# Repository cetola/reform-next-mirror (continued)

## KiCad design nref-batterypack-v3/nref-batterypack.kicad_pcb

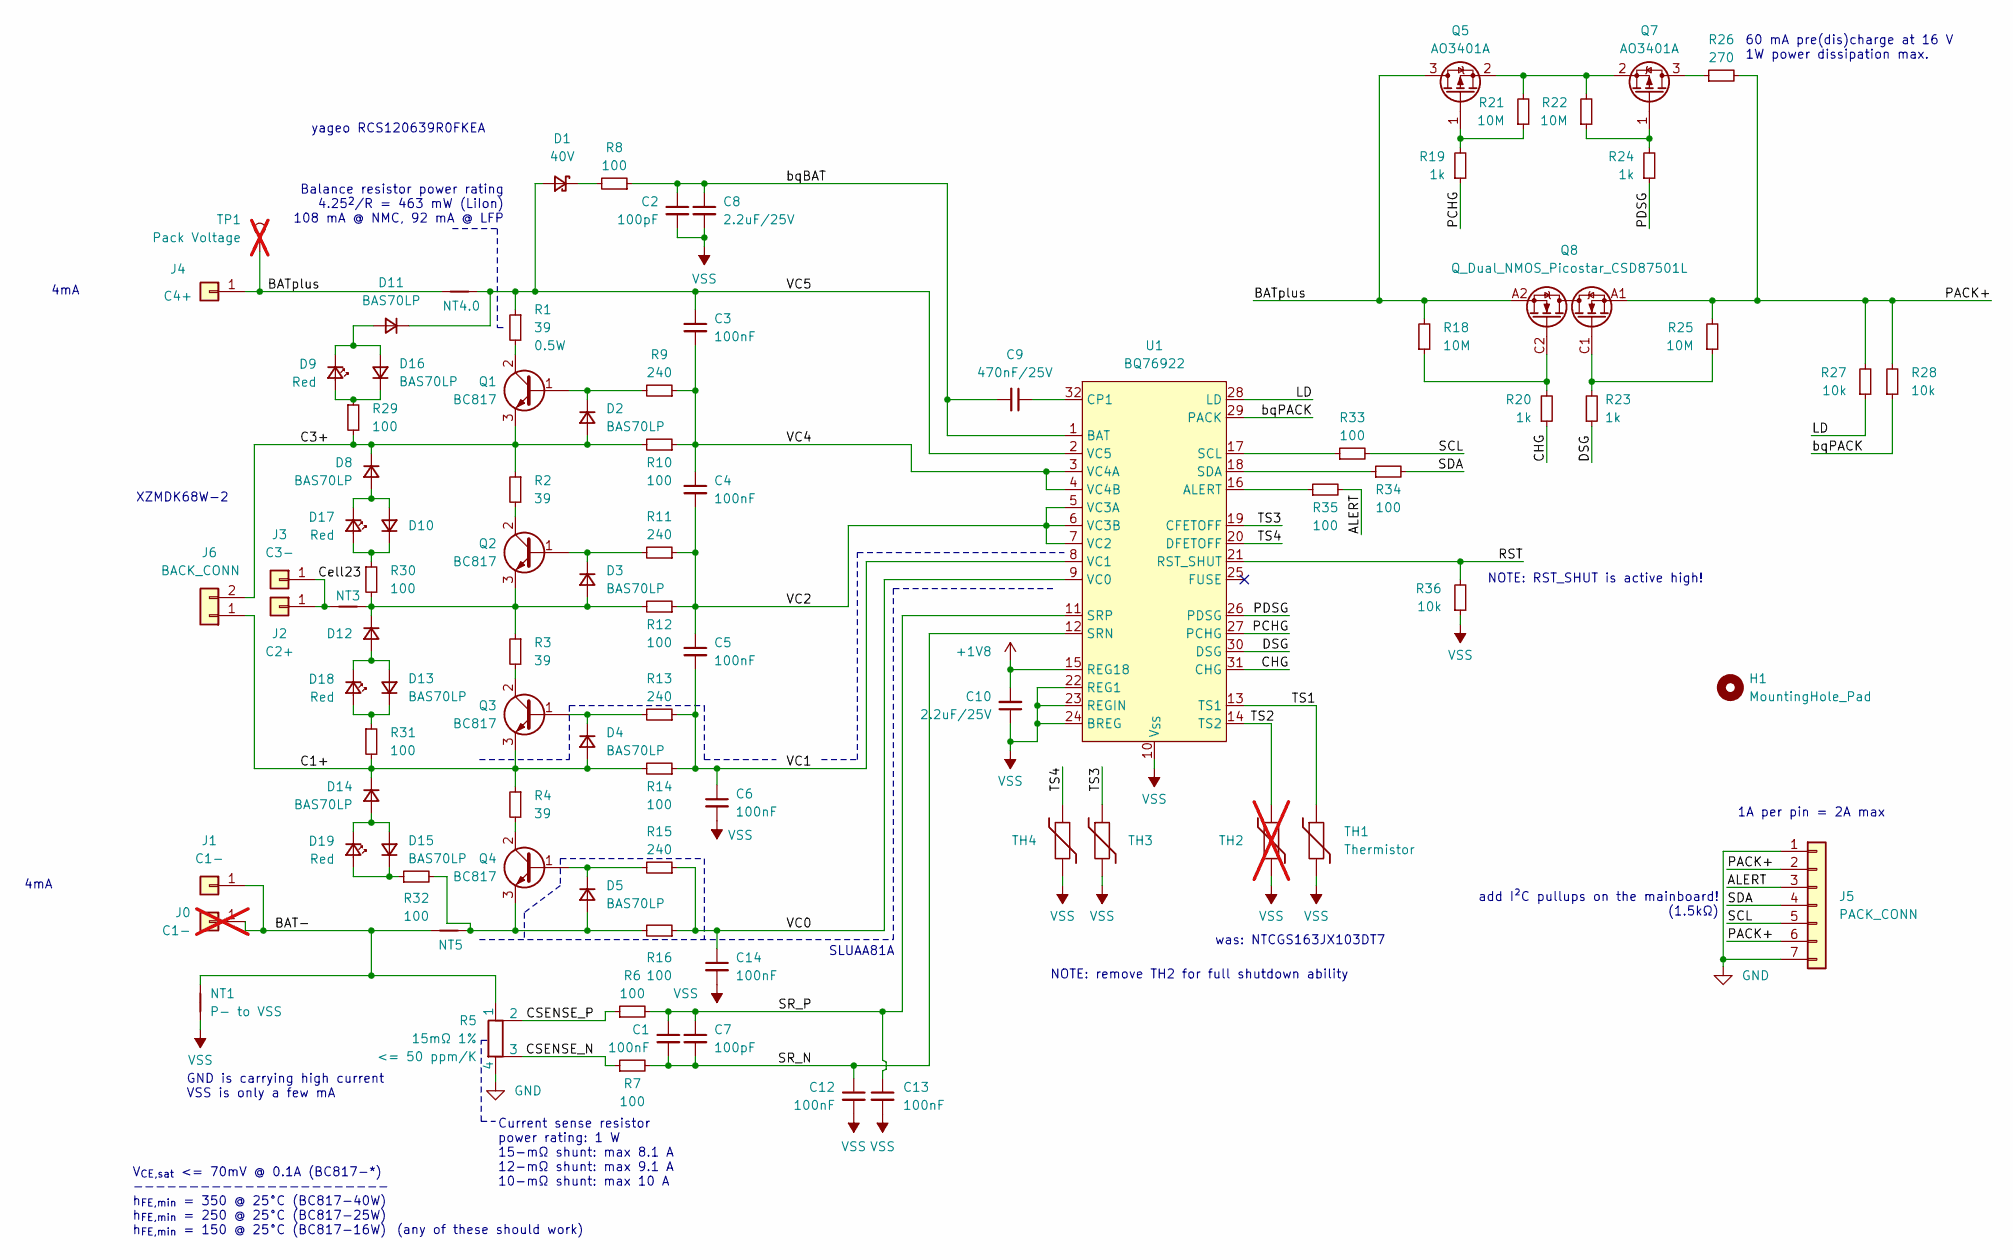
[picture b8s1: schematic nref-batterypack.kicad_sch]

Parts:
C1, C3, C4, C5, C6, C12, C13, C14: 100nF; C_0402_1005Metric; MPN CL05B104KO5NNNC; LCSC C1525
C2, C7: 100pF; C_0402_1005Metric; MPN 0402CG101J500NT; LCSC C1546
C8, C10: 2.2uF/25V; C_0402_1005Metric; MPN GRM155R61E225ME15D; LCSC C72203
C9: 470nF/25V; C_0402_1005Metric; MPN CL05A474KA5NNNC; LCSC C92361
D1: 40V; D_SOD-323; MPN B140WS-7; LCSC C95171
D2, D3, D4, D5, D8, D10, D11, D12, D13, D14, D15, D16: BAS70LP; D_SOD-882; MPN BAS70LP-7B; LCSC C134385
D9, D17, D18, D19: Red; LED_0402_1005Metric; MPN NCD0402R1; LCSC C130719
H1: MountingHole_Pad; MountingHole_2.2mm_M2
J0: C1-; TestPoint_Pad_D1.0mm; MPN DNP; not fitted
J1: C1-; MYOUNG_MY-FJ-115; MPN MY-FJ-115; LCSC C5457098
J2: C2+; Mill-Max_2036-X-57; MPN 2036-3-57-15-00-00-03-0; LCSC C20777560
J3: C3-; MYOUNG_MY-FJ-115; MPN MY-FJ-115; LCSC C5457098
J4: C4+; Mill-Max_2036-X-57; MPN 2036-3-57-15-00-00-03-0; LCSC C20777560
J5: PACK_CONN; JST_SH_BM07B-SRSS-TB_1x07-1MP_P1.00mm_Vertical; MPN BM07B-SRSS-TB; LCSC C160393
J6: BACK_CONN; JST_SH_SM02B-SRSS-TB_1x02-1MP_P1.00mm_Horizontal; MPN SM02B-SRSS-TB; LCSC C160402
NT1: P- to VSS; NetTie-2_SMD_Pad0.5mm; MPN DNP
NT3, NT5: NetTie-2_SMD_Pad0.5mm; MPN DNP
NT4.0: P- to GND; NetTie-2_SMD_Pad0.5mm; MPN DNP
Q1, Q2, Q3, Q4: BC817; SOT-23; MPN BC817-25LT1G; LCSC C12766
Q5, Q7: AO3401A; SOT-23; MPN AO3401A; LCSC C15127
Q8: Q_Dual_NMOS_Picostar_CSD87501L; TI_PICOSTAR_LGA-10_3.37x1.47mm_P0.65mm; MPN CSD87501L; LCSC C2841784
R1, R2, R3, R4: 39; R_1210_3225Metric; MPN FRP1206J390 TS; LCSC C5713422
R5: 15mΩ 1%; R_Shunt_Kelvin_Littlefuse_L4CA; MPN PE0612FKF070R015L; LCSC C6142742
R6, R7, R8, R10, R12, R14, R16, R29, R30, R31, R32, R33, R34, R35: 100; R_0402_1005Metric; MPN 0402WGF1000TCE; LCSC C25076
R9, R11, R13, R15: 240; R_0402_1005Metric; MPN RC0402FR-07240RL; LCSC C114755
R18, R21, R22, R25: 10M; R_0402_1005Metric; MPN RC0402FR-0710ML; LCSC C138067
R19, R20, R23, R24: 1k; R_0402_1005Metric; MPN 0402WGF1001TCE; LCSC C11702
R26: 270; R_1812_4532Metric; MPN GR1812J270RT4G00; LCSC C49656236
R27, R28, R36: 10k; R_0402_1005Metric; MPN 0402WGF1002TCE; LCSC C25744
TH1, TH3, TH4: Thermistor; R_0402_1005Metric; MPN CMFX 103F3435; LCSC C2889040
TH2: Thermistor; R_0402_1005Metric; MPN NTCGS103JX103DT7; LCSC C24890359; not fitted
TP1: Pack Voltage; TestPoint_Pad_1.0x1.0mm; MPN DNP; not fitted
U1: BQ76922; Texas_RSN_WQFN-32-1EP_4x4mm_P0.4mm_EP2.8x2.8mm; MPN BQ76922; LCSC C33651534

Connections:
+1V8: C10.2, U1.15 (REG18)
/ALERT: J5.3, R35.2
/BAT-: J0.1 (Pin_1_1), J1.1 (Pin_1_1), NT1.2, NT5.2, R5.1
/BATplus: J4.1 (Pin_1_1), NT4.0.2, Q5.3 (D), Q8.A2 (S2), Q8.B2 (S2), Q8.D2 (S2), Q8.E2 (S2), R18.2, TP1.1 (1_1)
/C1+: D4.2 (A), D14.1 (K), J6.1, Q3.3 (E), R4.1, R14.2, R31.2
/C3+: D2.2 (A), D8.1 (K), J6.2, Q1.3 (E), R2.1, R10.2, R29.2
/CHG: R20.1, U1.31 (CHG)
/CSENSE_N: R5.3, R7.1
/CSENSE_P: R5.2, R6.1
/Cell23: J2.1 (Pin_1_1), J3.1 (Pin_1_1), NT3.2
/DSG: R23.1, U1.30 (DSG)
/LD: R27.1, U1.28 (LD)
/PACK+: J5.2, J5.6, Q8.A1 (S1), Q8.B1 (S1), Q8.D1 (S1), Q8.E1 (S1), R25.2, R26.2, R27.2, R28.2
/PCHG: R19.1, U1.27 (PCHG)
/PDSG: R24.1, U1.26 (PDSG)
/RST: R36.2, U1.21 (RST_SHUT)
/SCL: J5.5, R33.2
/SDA: J5.4, R34.2
/SR_N: C1.2, C7.2, C12.1, R7.2, U1.12 (SRN)
/SR_P: C1.1, C7.1, C13.1, R6.2, U1.11 (SRP)
/TS1: TH1.1, U1.13 (TS1)
/TS2: TH2.1, U1.14 (TS2)
/TS3: TH3.1, U1.19 (CFETOFF)
/TS4: TH4.1, U1.20 (DFETOFF)
/VC0: C14.1, R15.1, R16.1, U1.9 (VC0)
/VC1: C5.2, C6.1, R13.1, R14.1, U1.8 (VC1)
/VC2: C4.2, C5.1, R11.1, R12.1, U1.5 (VC3A), U1.6 (VC3B), U1.7 (VC2)
/VC4: C3.2, C4.1, R9.1, R10.1, U1.3 (VC4A), U1.4 (VC4B)
/VC5: C3.1, D1.2 (A), D11.1 (K), NT4.0.1, R1.1, U1.2 (VC5)
/bqBAT: C2.1, C8.1, C9.2, R8.1, U1.1 (BAT)
/bqPACK: R28.1, U1.29 (PACK)
GND: J5.1, J5.7, R5.4
unnamed: D1.1 (K), R8.2
unnamed: D2.1 (K), Q1.1 (B), R9.2
unnamed: D3.1 (K), Q2.1 (B), R11.2
unnamed: D4.1 (K), Q3.1 (B), R13.2
unnamed: D5.2 (A), NT5.1, Q4.3 (E), R16.2, R32.2
unnamed: D5.1 (K), Q4.1 (B), R15.2
unnamed: D8.2 (A), D10.2 (A), D17.1 (K)
unnamed: D10.1 (K), D17.2 (A), R30.1
unnamed: D9.1 (K), D11.2 (A), D16.2 (A)
unnamed: D12.2 (A), D13.2 (A), D18.1 (K)
unnamed: D3.2 (A), D12.1 (K), NT3.1, Q2.3 (E), R3.1, R12.2, R30.2
unnamed: D13.1 (K), D18.2 (A), R31.1
unnamed: D14.2 (A), D15.2 (A), D19.1 (K)
unnamed: D15.1 (K), D19.2 (A), R32.1
unnamed: D9.2 (A), D16.1 (K), R29.1
unnamed: Q1.2 (C), R1.2
unnamed: Q2.2 (C), R2.2
unnamed: Q3.2 (C), R3.2
unnamed: Q4.2 (C), R4.2
unnamed: Q5.1 (G), R19.2, R21.1
unnamed: Q5.2 (S), Q7.2 (S), R21.2, R22.2
unnamed: Q7.3 (D), R26.1
unnamed: Q7.1 (G), R22.1, R24.2
unnamed: Q8.C1 (G1), R23.2, R25.1
unnamed: Q8.C2 (G2), R18.1, R20.2
unnamed: R35.1, U1.16 (ALERT)
unnamed: C9.1, U1.32 (CP1)
unnamed: R33.1, U1.17 (SCL)
unnamed: R34.1, U1.18 (SDA)
VSS: C2.2, C6.2, C8.2, C10.1, C12.2, C13.2, C14.2, NT1.1, R36.1, TH1.2, TH2.2, TH3.2, TH4.2, U1.10 (V_{SS}), U1.22 (REG1), U1.23 (REGIN), U1.24 (BREG), U1.33 (EP)

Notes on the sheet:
4mA
NOTE: RST_SHUT is active high!
GND is carrying high current VSS is only a few mA
XZMDK68W-2
NOTE: remove TH2 for full shutdown ability
was: NTCGS163JX103DT7
V_{CE,sat} <= 70mV @ 0.1A (BC817-*) ----------------------- h_{FE,min} = 350 @ 25°C (BC817-40W) h_{FE,min} = 250 @ 25°C (BC817-25W) h_{FE,min} = 150 @ 25°C (BC817-16W)
(any of these should work)
1A per pin = 2A max
60 mA pre(dis)charge at 16 V 1W power dissipation max.
Current sense resistor power rating: 1 W 15-mΩ shunt: max 8.1 A 12-mΩ shunt: max 9.1 A 10-mΩ shunt: max 10 A
add I²C pullups on the mainboard! (1.5kΩ)
yageo RCS120639R0FKEA
Balance resistor power rating 4.25^{2}/R = 463 mW (LiIon) 108 mA @ NMC, 92 mA @ LFP
SLUAA81A

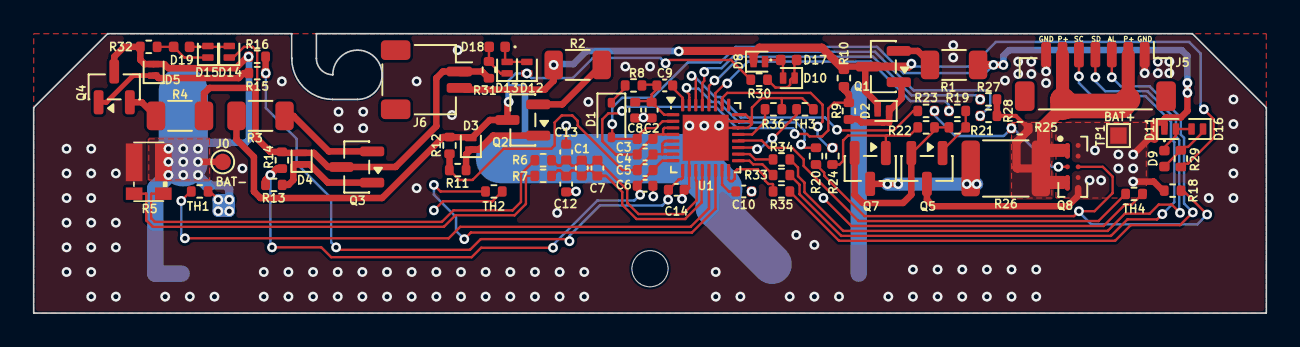
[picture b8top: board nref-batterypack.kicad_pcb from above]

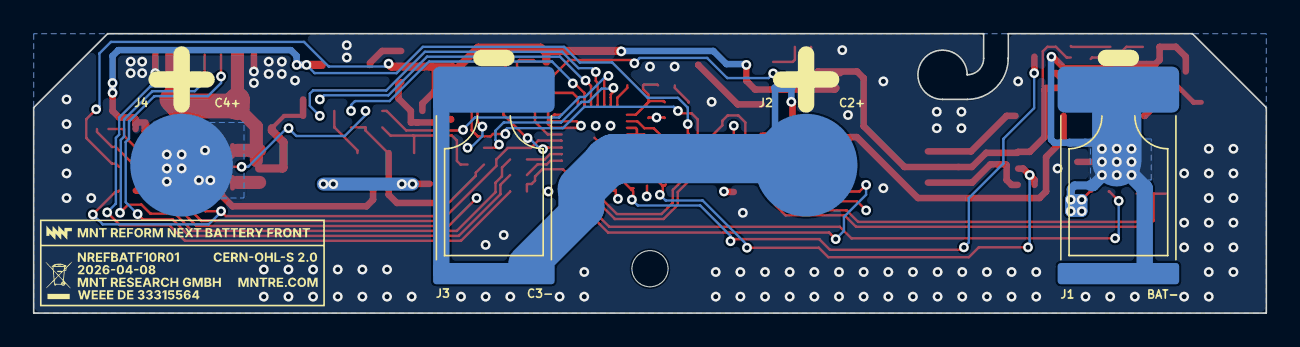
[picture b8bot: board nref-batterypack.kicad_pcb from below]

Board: 4 copper layers, 75.0 x 17.0 mm, 90 parts (7 on the bottom side), 62 nets.

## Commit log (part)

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2024-02-22 add batterypack pcb sketch
2024-02-22 add motherboard pcb early WIP
2024-02-22 add 202401 case proto and fc assembly
2024-03-25 add initial 4S battery pack with hs-switch
2024-04-28 motherboard: upgrade bucks to lm62460; some power layout
2024-04-29 motherboard: lots of connector shuffling and schematics
2024-04-30 motherboard: continue design; almost feature complete
2024-05-24 motherboard: update battery pack connectors, pcie lanes
2024-05-25 motherboard: some initial routing, mostly power
2024-05-27 ports test
2024-05-28 wip of the new version with another bms ic
2024-06-01 motherboard: drv_sup diodes, battery and charger i2c and alerts
2024-06-01 motherboard: consolidate switches and jumpers into one 8x1.27mm dip, liion/lifepo switch
2024-06-04 add a readme
2024-06-05 motherboard: connect extra pcie lanes
2024-06-05 motherboard: schematic done for d-1?
2024-06-05 lots of motherboard routing
2024-06-06 mb: swap some intersecting connectors; more routing
2024-06-07 mb routing snapshot
2024-06-07 mb silkscreen cleaned up
2024-06-07 mb fully routed, logo added
2024-06-11 ports-one WIP
2024-06-11 ports-two initial
2024-06-11 motherboard d-1 production snapshot
2024-06-12 ports one: some routing
2024-06-13 ports 1 routing, ports 2 location tweaks
2024-06-14 ports one: more design and more routing
2024-06-17 motherboard: specify all parts, complete BOM
2024-06-20 ports-one snapshot
2024-06-20 ports two: initial (mostly complete) schematic
2024-06-21 ports two: rough placement of components
2024-06-21 motherboard: add bringup notes to schematic
2024-06-21 batterypack and ports one snapshot
2024-06-21 update README, images
2024-06-21 add mechanical integration 20240604 (ondsel freecad)
2024-06-25 fix some images
2024-06-27 sysctl: first firmware, can negotiate PD
2024-07-04 ports-two: hdmi routing snapshot
2024-07-04 ports two: usb snapshot
2024-07-05 port board two fully routed
2024-07-25 ports two bom adjustments
2024-07-25 WIP batterypack-top polishing
2024-07-26 batterypack: finish front d-1, add back d-1
2024-07-28 v2 of the bms now based on the final outline
2024-07-30 batterypack: pick parts
2024-08-15 fix load switch nmos and gate prot diode polarity
2024-08-15 WIP camera board
2024-08-19 WIP trackpad
2024-08-20 docs: add ports one/two specs and drawings
2024-08-20 add port board three spec
2024-08-20 port boards spec: correct some links/images
2024-08-20 remove obsolete graphic
2024-08-20 add photos, battery system docs
2024-08-20 sysctl: implement charger and pack monitor comms
2024-08-20 add hdmi-edp adapter v2 sources
2024-08-22 trackpad: add first button board design d-1
2024-08-22 camera: redesigned and fully routed
2024-08-23 camera: d-3 done, off to board house
2024-08-23 camera: add fpc adapter pcb
2024-09-24 add full 2024-09-24 case assembly as STEP
2024-11-08 WIP mobo d2 snapshot
2024-11-12 motherboard: d-2 routing snapshot (0 unrouted)
2024-11-18 motherboard d-2 routing complete
2024-11-26 trackpad buttons: move left and right button further out
2024-11-26 batterypack front/back: update board outline/mounting holes
2024-12-04 add port covers drawn by gretam
2024-12-12 wip: sysctl-fw: add support for second battery pack
2024-12-27 add trackpad mount 20241202 stl
2024-12-27 sysctl: WIP
2024-12-27 add WIP eDP cable schematic
2024-12-27 add latest PCB updates
2024-12-27 add latest case integration freecad file
2025-01-13 added reverse polarity indicator LEDs
    + silk on the back to indicate cell polarity
    + updated resistor values for balancing
    * better b2b chg, dsg fets
    + more testpoints
2025-01-13 motherboard: add some notes
2025-01-13 sysctl fw WIP
2025-01-20 update README about trackpad and camera
2025-01-20 fix trackpad image link
2025-02-25 add bq25792 charger to schematic
2025-02-26 remove old charger, add some cap values
2025-02-27 pick some more parts, connect everything
2025-02-27 mb: first routing for new charger ic
2025-02-28 mb: tuning of new charger routing
2025-03-06 mb: rp2350a routed half the way
2025-03-07 mb: fully routed, cleanup left to do
2025-03-07 mb: wip
2025-03-08 mb: further pcb cleanups
2025-03-10 mb: finished layout for d-3 sample production
2025-03-17 mb d-3: update BOM/parts for buying
2025-04-22 sysctl: build with sdk from OS
2025-04-25 sysctl fw: initial WIP for new charger, rp2350a
2025-04-30 sysctl: WIP balancing works on bq76922
2025-04-30 WIP tweak limits
2025-05-16 sysctl fw: add basic over/undervoltage control and pack detection
2025-05-20 sysctl-fw: implement basic gauge, fix charger limits/controls
2025-05-21 sysctl: recognize full charge, tweak charging voltage/current
2025-05-23 initial version incl component choices
2025-06-13 WIP import new pocket sysctl fw and start merging
2025-06-14 sysctl fw2: make it build
2025-06-17 WIP sysctl fw2
2025-07-02 batterypack: snapshot before merge
2025-07-02 snapshot before merge
2025-07-02 bpack-v3 first snapshot
2025-07-03 battpack v3 snapshot
2025-07-03 battpack v3 (front) rerouting complete
2025-07-03 battpack v3 (front): routing polishing, 3d models
2025-07-03 battpack v3 (front) silkscreen
2025-07-04 batterypack v3 front+back pcbs polished for ordering
2025-07-29 add current notes on various schematics
2025-08-01 usb3-redriver: add first pcb design
2025-08-11 motherboard: snapshot before d4
2025-08-11 motherboard: WIP some TVS, more notes
2025-08-11 motherboard d4: WIP HS re-routing
2025-08-15 WIP mb v4 re-routing snapshot
2025-08-18 WIP MB: add some notes
2025-08-18 mb v4: WIP routing snapshot, 39 left
2025-08-20 WIP D-4 fully routed, still needs polishing
2025-08-21 WIP motherboard d-4: schematics fixes, some protection, hdmi sda/scl fix
2025-08-21 routing snapshot before deskew
2025-08-21 motherboard d-4: deskew done
2025-08-21 motherboard d-4: lots of GND/copper/via polishing
2025-08-22 motherboard d-4: fix some pcie/usb ground issues
2025-08-22 motherboard d-4: fix some more pcie/usb ground issues
2025-08-22 motherboard d-4: deskew again
2025-08-22 motherboard d-4: update silkscreen
2025-08-22 motherboard d-4: final tweaks
2025-08-22 motherboard d-4: ordered samples
2025-09-24 sysctl-fw2: get dual pack charging into shape, adjustable current
2025-09-24 Add Trackpad KiCad project
2025-09-24 add various notes in schematics
2025-09-24 sysctl-fw2: flash needs -f for picotool sometimes
2025-09-24 sysctl-fw2: fix spi reported voltage/amps calc
2025-09-24 add pocket-reform-shared-fw until we have a lib/submodule
2025-09-24 add copy of fw related scripts from pocket-reform
2025-09-26 sysctl-fw2: really fix spi reported voltage/amps calc
2025-09-28 next-sysctl-fw: replace sleep_ms calls in interrupt handlers
2025-10-03 add cable drawings (preliminary)
2025-10-03 flex: add WIP sound cable (6mm too short)
2025-10-03 flex: add WIP usb3 cable
2025-10-03 flex: add WIP pcie cable
2025-10-22 camera-adapter: mech. and routing update
2025-10-24 ports-one: snapshot before d2
2025-10-24 ports-one: WIP construction site
2025-10-31 ports-one: schematics with new mux, local 5v, hard reset switch
2025-10-31 ports-one: add redriver, routing WIP
2025-11-04 ports-one: add redriver circuit
2025-11-05 ports-one: routing snapshot
2025-11-07 WIP nref-ports-one: routing done, 3d checks to do
2025-11-12 ports-one: exchange pca chip, polish, add sbu header
2025-11-14 ports-one: BOM update
2025-11-15 sysctl-fw2: clip uart reporting
2025-11-19 ports-one: polishing/part selections
2025-11-19 WIP ports-two redesign
2025-11-19 ports-two: footprints
2025-11-20 ports-two: more routing
2025-11-25 commit various flex changes
2025-11-25 commit various notes / polishing for ports-one and ports-two
2025-12-09 ports-one: add TODOs after hw debugging
2025-12-09 ports-two: add TODOs after hw debugging
2025-12-16 ports-one: fix u9 pinout; remove r23
2026-01-10 sysctl-fw2: implement changes for new port board left incl usb-c power mux; fix battery pack shutdown/uv mode
2026-01-10 sysctl-fw2: revert extras
2026-01-10 sysctl-fw2: tweak shutdown config
2026-03-23 MB: add notes
2026-03-23 WIP: mb: 2280 SSD
2026-03-25 mainboard: finish R-1 routing
2026-03-27 sysctl-fw: experimentally accept datarole switch; turn off 5v usb host power when switching to power sink
2026-03-27 PCBs: add various notes
2026-03-27 MB WIP: one todo left (usb2 switcheroo)
2026-03-31 WIP mb: add countless usb muxes and usb uart
2026-04-01 mainboard: 1.0 r1 pcb done
2026-04-01 mainboard 1.0: part choices
2026-04-01 mainboard 1.0: pcb adjustment for part choices
2026-04-09 batterypack back/front: polishing for production
2026-04-09 mainboard: production parts
2026-04-09 trackpad sensor: redesign pcb shape for production
2026-05-21 SC: mb usb switches support, WIP debug stuff
2026-06-16 ports-two: snapshot of r2 before switch to nxp redriver
